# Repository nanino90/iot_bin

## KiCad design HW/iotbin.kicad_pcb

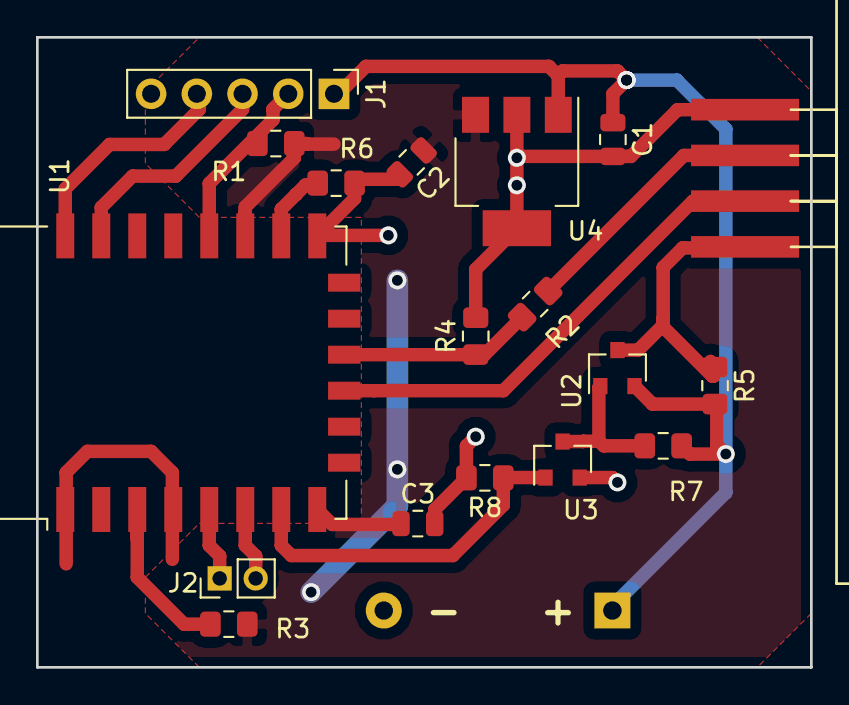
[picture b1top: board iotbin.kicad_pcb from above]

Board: 2 copper layers, 43.0 x 35.0 mm, 19 parts (1 on the bottom side), 17 nets.

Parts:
BT1: Battery; Battery_AAAx3_no_hole
C1, C2, C3: CAP; C_0805_2012Metric
J1: Conn_01x05_Male; PinHeader_1x05_P2.54mm_Vertical
J2: Conn_01x02_Male; PinHeader_1x02_P2.00mm_Vertical
P1: hc-sr04; HC-SR04_flat_down
R1, R3, R6: 10K; R_0805_2012Metric_Pad1.15x1.40mm_HandSolder
R2, R8: 1K; R_0805_2012Metric_Pad1.15x1.40mm_HandSolder
R4: 2K; R_0805_2012Metric_Pad1.15x1.40mm_HandSolder
R5: 0; R_0805_2012Metric_Pad1.15x1.40mm_HandSolder
R7: 1M; R_0805_2012Metric_Pad1.15x1.40mm_HandSolder
U1: ESP-12F; ESP-12E
U2: FDV302P; SOT-23
U3: FDV303N; SOT-23
U4: AP2204RB-3.3; SOT-223-3_TabPin2

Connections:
/3V3: C2.1, C3.1, R1.2, R3.1, U1.8, U1.17, U4.3
/5V_S: P1.4, R5.1, U2.3
/BAT: BT1.1, C1.1, J1.1, R5.2, R7.2, U2.2, U4.1
/Echo: P1.2, R2.1
/ON: R8.1, U1.7, U3.1
/RST: U1.1, U1.4
/Trig: P1.3, U1.11
GND: BT1.2, C1.2, C2.2, C3.2, J1.5, P1.1, R4.2, R6.2, R8.2, U1.15, U3.2, U4.2
unnamed: J1.2, R1.1, U1.18
unnamed: J1.3, U1.21
unnamed: J1.4, U1.22
unnamed: J2.1, U1.5
unnamed: J2.2, U1.6
unnamed: R2.2, R4.1, U1.12
unnamed: R3.2, U1.3
unnamed: R6.1, U1.16
unnamed: R7.1, U2.1, U3.3

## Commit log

2018-09-12 Added FW init
2018-09-12 Setting libraries in kicad
2018-09-13 Tested power modes, added libraries, updated HW
2018-09-17 Finished board+gerber
2018-09-18 Sent gerbers 1.2
2018-09-21 Added measure level function and working with real hardware
2018-09-21 Added flow diagraman
